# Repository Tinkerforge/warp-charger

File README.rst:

WARP Charger
============

You can find more information, technical details etc. about WARP Chargers at http://warp-charger.com.

This repository contains the source of this web site, all released firmwares, the manual and some additional information.

.. BEGIN WARP REPOSITORIES (managed block, generated from esp32-firmware/repo_overview.rst - do not edit by hand, run update_repo_overview.py instead)

WARP Repositories
-----------------

This is an overview of all repositories that make up the WARP Charger and
WARP Energy Manager ecosystem.

Please report **any** issue concerning WARP hard- or software in the
`esp32-firmware`_ repository, no matter which repository it originates from.

Software
~~~~~~~~

- `esp32-firmware`_ - Source code of the ESP32 firmware shared between all WARP Chargers and Energy Managers

Libraries used by the firmware:

- `tfjson`_ - SAX style JSON serializer and deserializer
- `tfnetwork`_ - Modbus TCP server and client implementation
- `tfocpp`_ - OCPP 1.6 implementation
- `tftools`_ - Miscellaneous tools and helpers

Remote access:

- `esp32-remote-access`_ - Source code of the my.warp-charger.com remote access server

Documentation, tools and integrations:

- `warp-charger`_ - Source code of (docs.)warp-charger.com and the printed manual, released firmwares, datasheets and documents, as well as some tools and hardware design files
- `api.warp-charger.com`_ - Serves APIs that are used by WARP Chargers to obtain relevant public information like day ahead prices
- `vislog.warp-charger.com`_ - Visualizes WARP Charger logs and EVSE debug protocols
- `dbus-warp-charger`_ - Integrates WARP Chargers into a Victron Energy Venus OS device (e.g. Cerbo GX)

WARP Charger Hardware
~~~~~~~~~~~~~~~~~~~~~~

WARP4 Charger
"""""""""""""

*Current charger generation.*

- `warp-esp32-ethernet-v2-brick`_ - Hardware design files of the WARP ESP32 Ethernet Brick 2.0
- `warp-esp32-ethernet-v2-co-bricklet`_ - Firmware source code of the WARP ESP32 Ethernet 2.0 Co Bricklet (co-processor)
- `evse-v4-bricklet`_ - Hardware design files of the EVSE 4.0 Bricklet (firmware shared with the EVSE 2.0 Bricklet)
- `nfc-bricklet`_ - Firmware source code and hardware design files of the NFC Bricklet

WARP3 Charger
"""""""""""""

- `warp-esp32-ethernet-brick`_ - Hardware design files of the WARP ESP32 Ethernet Brick
- `evse-v3-bricklet`_ - Hardware design files of the EVSE 3.0 Bricklet (firmware shared with the EVSE 2.0 Bricklet)
- `nfc-bricklet`_ - Firmware source code and hardware design files of the NFC Bricklet

WARP2 Charger
"""""""""""""

- `esp32-ethernet-brick`_ - Hardware design files of the ESP32 Ethernet Brick
- `evse-v2-bricklet`_ - Firmware source code and hardware design files of the EVSE 2.0 Bricklet
- `nfc-bricklet`_ - Firmware source code and hardware design files of the NFC Bricklet

WARP1 Charger
"""""""""""""

- `esp32-brick`_ - Hardware design files of the ESP32 Brick
- `evse-bricklet`_ - Firmware source code and hardware design files of the EVSE Bricklet
- `rs485-bricklet`_ - Firmware source code and hardware design files of the RS485 Bricklet

WARP Energy Manager Hardware
~~~~~~~~~~~~~~~~~~~~~~~~~~~~~~

WARP Energy Manager 2.0
"""""""""""""""""""""""

*Current energy manager generation.*

- `esp32-ethernet-brick`_ - Hardware design files of the ESP32 Ethernet Brick
- `warp-energy-manager-v2-bricklet`_ - Firmware source code and hardware design files of the WARP Energy Manager 2.0 Bricklet
- `warp-front-panel-bricklet`_ - Firmware source code and hardware design files of the WARP Front Panel Bricklet

WARP Energy Manager 1.0
"""""""""""""""""""""""

- `esp32-ethernet-brick`_ - Hardware design files of the ESP32 Ethernet Brick
- `warp-energy-manager-bricklet`_ - Firmware source code and hardware design files of the WARP Energy Manager Bricklet

Forked/patched projects
~~~~~~~~~~~~~~~~~~~~~~~~~

- `arduino-esp32`_
- `esp32-arduino-libs`_
- `WireGuard-ESP32-Arduino`_

.. Link targets: One definition per repository, keep in sync with the lists above.

.. _esp32-firmware: https://github.com/Tinkerforge/esp32-firmware
.. _tfjson: https://github.com/Tinkerforge/tfjson
.. _tfnetwork: https://github.com/Tinkerforge/tfnetwork
.. _tfocpp: https://github.com/Tinkerforge/tfocpp
.. _tftools: https://github.com/Tinkerforge/tftools
.. _esp32-remote-access: https://github.com/Tinkerforge/esp32-remote-access
.. _warp-charger: https://github.com/Tinkerforge/warp-charger
.. _api.warp-charger.com: https://github.com/Tinkerforge/api.warp-charger.com
.. _vislog.warp-charger.com: https://github.com/Tinkerforge/vislog.warp-charger.com
.. _dbus-warp-charger: https://github.com/Tinkerforge/dbus-warp-charger
.. _warp-esp32-ethernet-v2-brick: https://github.com/Tinkerforge/warp-esp32-ethernet-v2-brick
.. _warp-esp32-ethernet-v2-co-bricklet: https://github.com/Tinkerforge/warp-esp32-ethernet-v2-co-bricklet
.. _evse-v4-bricklet: https://github.com/Tinkerforge/evse-v4-bricklet
.. _nfc-bricklet: https://github.com/Tinkerforge/nfc-bricklet
.. _warp-esp32-ethernet-brick: https://github.com/Tinkerforge/warp-esp32-ethernet-brick
.. _evse-v3-bricklet: https://github.com/Tinkerforge/evse-v3-bricklet
.. _esp32-ethernet-brick: https://github.com/Tinkerforge/esp32-ethernet-brick
.. _evse-v2-bricklet: https://github.com/Tinkerforge/evse-v2-bricklet
.. _esp32-brick: https://github.com/Tinkerforge/esp32-brick
.. _evse-bricklet: https://github.com/Tinkerforge/evse-bricklet
.. _rs485-bricklet: https://github.com/Tinkerforge/rs485-bricklet
.. _warp-energy-manager-v2-bricklet: https://github.com/Tinkerforge/warp-energy-manager-v2-bricklet
.. _warp-front-panel-bricklet: https://github.com/Tinkerforge/warp-front-panel-bricklet
.. _warp-energy-manager-bricklet: https://github.com/Tinkerforge/warp-energy-manager-bricklet
.. _arduino-esp32: https://github.com/Tinkerforge/arduino-esp32
.. _esp32-arduino-libs: https://github.com/Tinkerforge/esp32-arduino-libs
.. _WireGuard-ESP32-Arduino: https://github.com/Tinkerforge/WireGuard-ESP32-Arduino

.. END WARP REPOSITORIES

Repository Content
------------------

documents/:
 * Contains test reports, data sheets and manuals for the WARP Charger itself and used components

firmwares/:
 * All released firmwares as well as their .elf files used for decoding stack traces and further debugging

hardware/:
 * Contains KiCad project files for some custom PCBs used in the WARP Charger

label/:
 * Scripts and other files used to create and print the type label sticker

manual/:
 * LaTeX source and used resources for the manual

warp-charger.com/:
 * The source of the WARP Charger web site (this site is deprecated, the old hand-written html site has been moved to a wordpress)

Firmwares
---------

The firmwares folder contains all released firmwares as bin files. These can be flashed
using the web interface or over USB using https://github.com/espressif/esptool/ at offset 0x1000.
The folder also contains the ELF files with debug information.

Hardware
--------

Parts of the hardware are designed with the open source EDA Suite KiCad
(http://www.kicad.org). Before you are able to open the files,
you have to install the Tinkerforge kicad-libraries
(https://github.com/Tinkerforge/kicad-libraries). You can either clone
them directly in hardware/ or clone them in a separate folder and
symlink them into hardware/
(ln -s kicad_path/kicad-libraries project_path/hardware). After that you
can open the .pro file in hardware/ with KiCad and from there view and
modify the schematics and the PCB layout.

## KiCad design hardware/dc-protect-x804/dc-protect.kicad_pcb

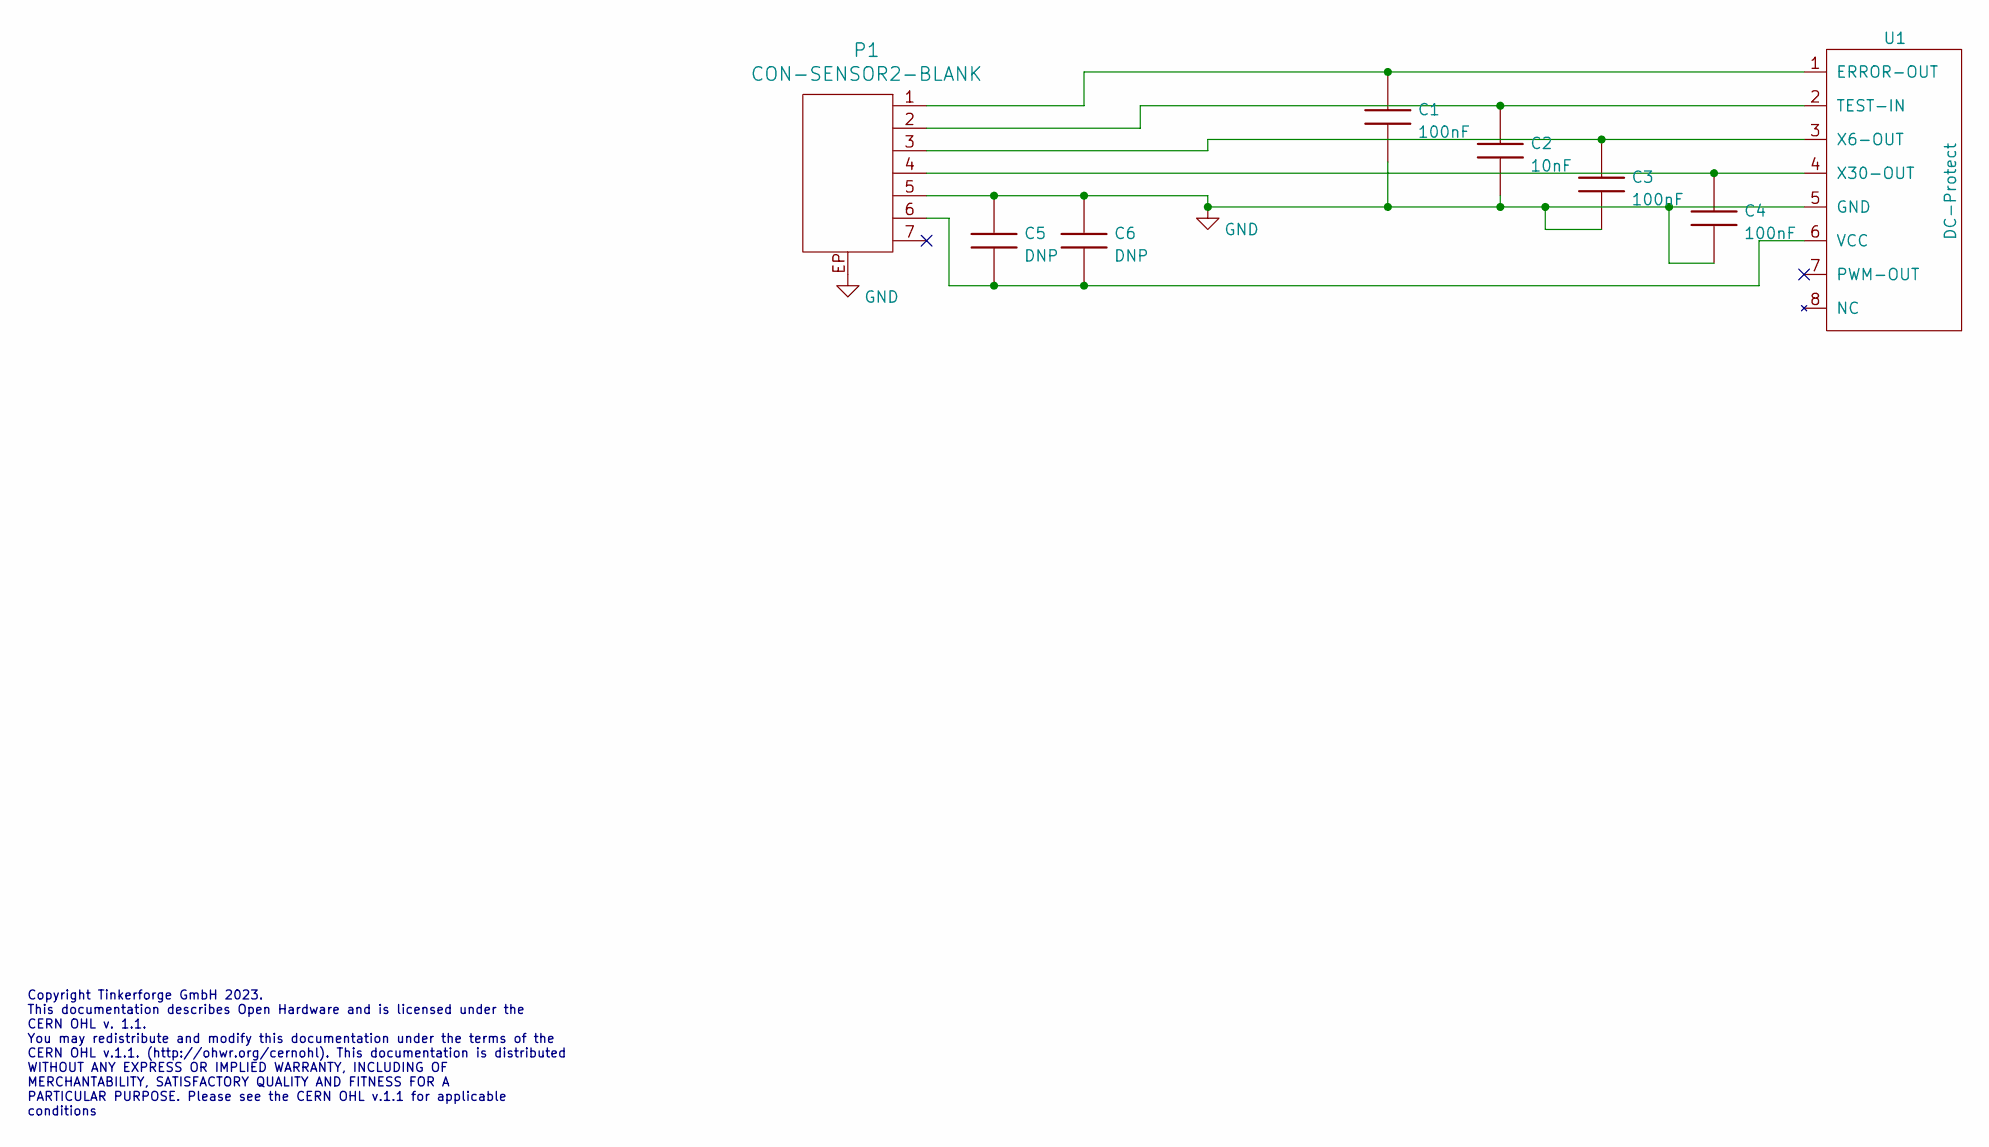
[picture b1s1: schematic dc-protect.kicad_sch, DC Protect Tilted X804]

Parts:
C1, C3, C4: 100nF; C0402E
C2: 10nF; C0402E
C5: DNP; C0805E
C6: DNP; C0402E
P1: CON-SENSOR2-BLANK; CON-SENSOR2_180
U1: DC-Protect

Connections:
GND: C1.2, C2.2, C3.2, C4.2, C5.1, C6.1, P1.5, P1.EP, U1.5 (GND)
unnamed: C1.1, P1.1, U1.1 (ERROR-OUT)
unnamed: C2.1, P1.2, U1.2 (TEST-IN)
unnamed: C3.1, P1.3, U1.3 (X6-OUT)
unnamed: C4.1, P1.4, U1.4 (X30-OUT)
unnamed: C5.2, C6.2, P1.6, U1.6 (VCC)

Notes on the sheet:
Copyright Tinkerforge GmbH 2023. This documentation describes Open Hardware and is licensed under the CERN OHL v. 1.1. You may redistribute and modify this documentation under the terms of the CERN OHL v.1.1. (http://ohwr.org/cernohl). This documentation is distributed WITHOUT ANY EXPRESS OR IMPLIE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

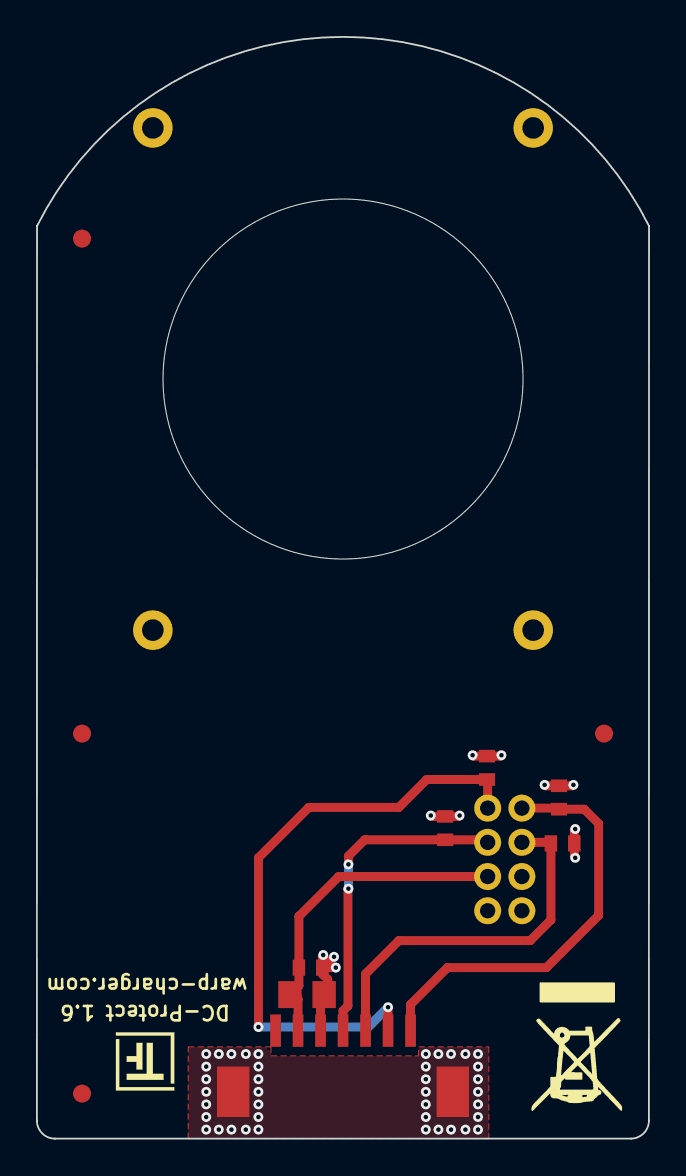
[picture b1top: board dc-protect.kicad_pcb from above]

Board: 2 copper layers, 34.0 x 61.2 mm, 13 parts (0 on the bottom side), 6 nets.

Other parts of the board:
Fiducial_Mark: VAL**; Fiducial_Mark
Fiducial_Mark#2, Fiducial_Mark#3, Fiducial_Mark#4: VAL**; Fiducial_Mark
VAL: WEEE_7mm

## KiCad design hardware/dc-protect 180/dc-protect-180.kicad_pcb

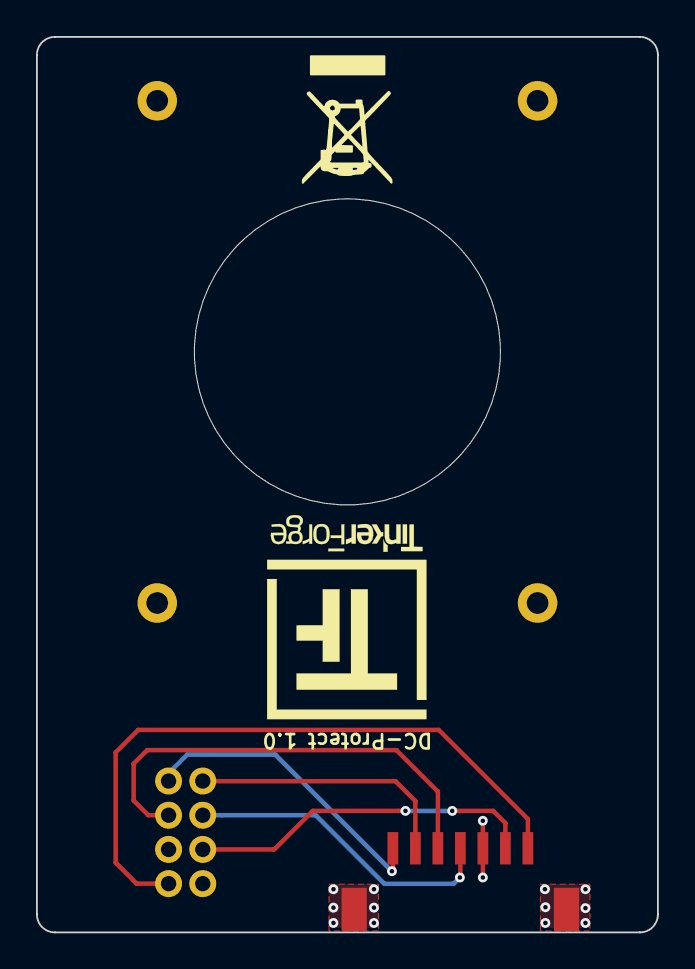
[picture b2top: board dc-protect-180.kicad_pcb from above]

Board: 2 copper layers, 34.5 x 49.8 mm, 3 parts (1 on the bottom side), 7 nets.

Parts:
P1: CON-SENSOR2-BLANK; CON-SENSOR2
U1: DC-Protect
VAL: WEEE_7mm

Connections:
GND: P1.5, P1.EP, U1.5
unnamed: P1.1, U1.1
unnamed: P1.2, U1.2
unnamed: P1.3, U1.3
unnamed: P1.4, U1.4
unnamed: P1.6, U1.6
unnamed: P1.7, U1.7

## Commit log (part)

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2026-05-28 docs: Move (WEM) charge tracker from energy manager to management.
2026-05-31 Move warp-charger.com to old.warp-charger.com
2026-05-31 Add new warp-charger.com homepage
2026-05-31 Remove unused server scripts (now handled by central cron.sh)
2026-05-31 WARP4-Charger -> WARP4 Charger
2026-05-31 build(deps): bump qs and express in /docs.warp-charger.com
    Bumps [qs](https://github.com/ljharb/qs) and [express](https://github.com/expressjs/express). These dependencies needed to be updated together.
    Updates `qs` from 6.14.2 to 6.15.2
    - [Changelog](https://github.com/ljharb/qs/blob/main/CHANGELOG.md)
    - [Commits](https://github.com/ljharb/qs/compare/v6.14.2...v6.15.2)
    Updates `express` from 4.22.1 to 4.22.2
    - [Release notes](https://github.com/expressjs/express/releases)
2026-05-31 Fix server npm directory
2026-05-31 add a lot of dots
2026-05-31 manuel: Improve wording, fix typos, remove todo-leftovers
2026-05-31 documents: Update WARP4 manual
2026-05-31 Improve naming consistency between english docs and web interface
2026-05-31 Fix charge management mixup
    confusingly it seems like we call the Charge Management "Charge Management",
    but then when we talk about the dynamic/static part about it, we
    call it load management.
2026-05-31 warp-charger.com: Fix Charge/Load Management mixup
2026-05-31 warp-charger.com: Add impact resistance
2026-05-31 warp-charger.com: Add anchors for documents
2026-05-31 warp-charger.com: Use same anchor name as old homepage
2026-06-01 Fix logo
2026-06-01 fix typo
2026-06-01 add faq
2026-06-01 appen technical specification
2026-06-01 warp-charger.com: Dont crop team photo on mobile
2026-06-01 Add company drone shot
2026-06-01 warp-charger.com: Add link for Made in Germany bento grid
2026-06-01 warp-charger.com: Fix icons and icon-links in mobile menu
2026-06-01 warp-charger.com: Improve language-switcher for mobile
2026-06-02 build(deps): bump webpack-dev-server in /docs.warp-charger.com
    Bumps [webpack-dev-server](https://github.com/webpack/webpack-dev-server) from 5.2.2 to 5.2.4.
    - [Release notes](https://github.com/webpack/webpack-dev-server/releases)
    - [Changelog](https://github.com/webpack/webpack-dev-server/blob/main/CHANGELOG.md)
    - [Commits](https://github.com/webpack/webpack-dev-server/compare/v5.2.2...v5.2.4)
    ---
    updated-dependencies:
2026-06-02 add features to technical details
2026-06-02 enhance technical spec
2026-06-02 improve technical spec
2026-06-02 increase charge tracker numbers: 7680 -> 32768 (new Firmware)
2026-06-02 docs: expand HA setup guide
2026-06-02 add more technical details
2026-06-02 build(deps): bump react from 19.2.6 to 19.2.7 in /docs.warp-charger.com
    Bumps [react](https://github.com/facebook/react/tree/HEAD/packages/react) from 19.2.6 to 19.2.7.
    - [Release notes](https://github.com/facebook/react/releases)
    - [Changelog](https://github.com/facebook/react/blob/main/CHANGELOG.md)
    - [Commits](https://github.com/facebook/react/commits/v19.2.7/packages/react)
    ---
    updated-dependencies:
2026-06-02 Add animation to image switcher
2026-06-02 warp-charger.com: Make the info button more visible
2026-06-02 Improve diagram step and pulse for mobile
2026-06-02 warp-charger.com: Make sure the info pulse stays of once pressed
2026-06-02 Use anchor for product tabs to make it sharable
2026-06-02 warp-charger.com: Implement newsletter registration
2026-06-03 build(deps): bump react-dom in /docs.warp-charger.com
    Bumps [react-dom](https://github.com/facebook/react/tree/HEAD/packages/react-dom) from 19.2.6 to 19.2.7.
    - [Release notes](https://github.com/facebook/react/releases)
    - [Changelog](https://github.com/facebook/react/blob/main/CHANGELOG.md)
    - [Commits](https://github.com/facebook/react/commits/v19.2.7/packages/react-dom)
    ---
    updated-dependencies:
2026-06-03 Add rounded borders and shadow to video
2026-06-03 warp-charger.com: Replace all ttfs with woff2.
2026-06-03 docs: Update modbus table.
2026-06-03 Add firmwares for WARP 2.11.0, WARP2 2.11.0, WARP3 2.11.0, WEM 2.7.0, WEM2 1.6.0, SEB 1.6.0.
2026-06-04 warp-charger.com: Update compile.sh for pre-compression
2026-06-04 warp-charger.com: Add find-an-electrician page
2026-06-04 warp-charger.com: Make electrician CTA more direct
2026-06-04 warp-charger.com: Just always call npm install when compile.sh is run
2026-06-04 Normalize phone numbers
2026-06-04 warp-charger.com: Add social share tags
    We need to make one 1200x630px image per page...
2026-06-05 add solaredge nexis support
2026-06-05 add kostal plenticore battery control
2026-06-05 fix eichrecht FAQ
2026-06-05 warp-charger.com: Update generated files.
2026-06-05 warp-charger.com: Let sections show up when 5% in viewport.
2026-06-05 docs: Document central management on chargers subpage.
2026-06-05 warp-charger.com: Normalize email addresses
    Use only email addresses that are part of the Impressum
2026-06-05 warp-charger.com: Remove double entry
2026-06-05 warp-charger.com: Update electricians
2026-06-05 add exhibition blogt
2026-06-05 fix faq
2026-06-05 warp-charger.com: Improve blog
2026-06-05 warp-charger.com: Improve electrician finder popup
2026-06-05 warp-charger.com: Allow swipe guesture for slider on mobile
2026-06-05 warp-charger.com: Add missing descriptive text for link
2026-06-05 warp-charger.com: Add mtime based cache-busting to static files
    We set "expires 1y;" in nginx
2026-06-05 warp-charger.com: Inline css to save a separate request
2026-06-05 warp-charger.com: Improve slider performance
2026-06-05 warp-charger.com: Make sure the video poster can be preloaded
2026-06-05 warp-charger.com: Defer diagram setup
2026-06-05 warp-charger.com: Add context to the "show more" link
    Even with aria info it was still flagged as bad seo/accessibility.
    It does look fine with the additional info the link directly.
2026-06-05 warp-charger.com: Improve font size and preload behavior
2026-06-05 warp-charger.com: Re-size/encode all images
    Now that the homepage is more mature we can resize all images
    to exact sizes that are actually needed.
2026-06-05 warp-charger.com: Re-encode images again
    Re-encode (from original) again. I was a bit too aggressive before.
    Some images got some obvious artifacts because of the qauality
    change in the webp encoding. We now just change the resolution
    of the images as needed, so there shouldn't be any recognizable
    difference in the image-quality now.
2026-06-08 warp-charger.com: Add bruns video
2026-06-08 warp-charger.com: Add WARP4 datasheet
2026-06-08 documents: Add WARP4_Datenblatt.pdf
2026-06-09 label: Patch length of SKU in data matrix code of package label
2026-06-09 docs: fix HA typos and grammar
2026-06-09 docs: add iobroker guide
2026-06-09 docs: add discovery options to MQTT introduction
2026-06-10 manual/warp4: Fix status widget colors.
2026-06-10 manual/warp4: Strip trailing whitespace.
2026-06-10 manual/warp4: Fix typos, wording, layout, etc.
2026-06-10 manual/warp4: Replace spare parts table with description.
2026-06-10 documents: Update WARP4 manual.
2026-06-10 add victron hint
2026-06-10 docs: fix typos and expand iobroker script
2026-06-10 label: Updates for WARP4
2026-06-10 label: Fix broken placeholder
2026-06-10 label: Fix WARP4 specific assert
2026-06-10 label: Fix version check
2026-06-10 label: Fix typo
2026-06-10 label: Use new wording for stand material
2026-06-10 label: Add custom cable to package label
2026-06-10 label: Add missing comma
2026-06-10 add preiskalender hint
2026-06-10 label: Fix title of internal label
2026-06-10 warp-charger.com: Update with bug-fixed videos
2026-06-10 docs: Update english translations
2026-06-10 docs: Improve english translations
    Fix some links, use consistant terminology etc
2026-06-11 build(deps): bump shell-quote in /docs.warp-charger.com
    Bumps [shell-quote](https://github.com/ljharb/shell-quote) from 1.8.3 to 1.8.4.
    - [Changelog](https://github.com/ljharb/shell-quote/blob/main/CHANGELOG.md)
    - [Commits](https://github.com/ljharb/shell-quote/compare/v1.8.3...v1.8.4)
    ---
    updated-dependencies:
    - dependency-name: shell-quote
2026-06-11 warp-charger.com: Update Made in Germany image
    Phoenix -> NMI
2026-06-11 docs: add openhab guide
2026-06-11 add elektrofreunde
2026-06-11 warp-charger.com: Fix grammer, typos
2026-06-12 docs: remove iobroker warning from MQTT introduction
2026-06-12 docs: add openhab translations and fix typos/grammar
2026-06-12 docs: update iobroker translation
2026-06-15 docs: Use consistant approach for different charger and EM generations
    Consistantly use "WARP Charger" and "WARP Energy Manager" to
    refer to any version. Only use WARPx Charger and WARP Energy Manager x.0
    when refering to a specific version.
2026-06-15 docs: Add proper backported docs for WARP1/2 and WEM1
2026-06-15 docs: Remove dependency and symlinks to tex-manual
    Also remove all unused images (only used in manual) and re-size
    some of the large images that need to be large for the print version
    of the manual.
    This idea to re-use the image folder from the manual got a bit out
    of hand because of the huge image sized that we have for WARP1/2
    manual.
2026-06-15 docs: Use same typography as warp-charger.com
    Just copies the font and most basic CSS.
2026-06-16 temporary fix of status page
2026-06-17 build(deps): bump dompurify in /docs.warp-charger.com
    Bumps [dompurify](https://github.com/cure53/DOMPurify) from 3.4.1 to 3.4.10.
    - [Release notes](https://github.com/cure53/DOMPurify/releases)
    - [Commits](https://github.com/cure53/DOMPurify/compare/3.4.1...3.4.10)
    ---
    updated-dependencies:
    - dependency-name: dompurify
2026-06-17 build(deps): bump launch-editor in /docs.warp-charger.com
    Bumps [launch-editor](https://github.com/vitejs/launch-editor) from 2.12.0 to 2.14.1.
    - [Commits](https://github.com/vitejs/launch-editor/compare/v2.12.0...v2.14.1)
    ---
    updated-dependencies:
    - dependency-name: launch-editor
    dependency-version: 2.14.1
2026-06-17 build(deps): bump ws in /docs.warp-charger.com
    Bumps and [ws](https://github.com/websockets/ws). These dependencies needed to be updated together.
    Updates `ws` from 7.5.10 to 7.5.11
    - [Release notes](https://github.com/websockets/ws/releases)
    - [Commits](https://github.com/websockets/ws/compare/7.5.10...7.5.11)
    Updates `ws` from 8.19.0 to 8.21.0
    - [Release notes](https://github.com/websockets/ws/releases)
2026-06-17 docs: add loxone setup guide (DE)
2026-06-17 docs: add template import image
2026-06-17 docs: Make sure xml files are downloaded
2026-06-18 firmwares: Add check for index file v3
2026-06-18 docs: add eebus notes to loxone
2026-06-19 add new blog
2026-06-19 add also blog
2026-06-20 docs: Add preliminary WARP4 installation video
2026-06-20 docs: Add WARP4 installation video
2026-06-22 warp-charger.com: Remove bogus entry
2026-06-22 warp-charger.com: Update gecoded json
2026-06-22 label: Rename the accessories label to extras label
    There will be an actual accessories label in the future.
    The now called extras label doesn't really include accessories,
    but modifications or additions to the normal charger build.
2026-06-23 label: Unify staging password file name.
2026-06-23 label: Also update .gitignore.
2026-06-24 docs: update eebus to include actors and client mode
2026-06-24 label: Add new accessories label
2026-06-25 firmwares: Add empty index file for WARP4
2026-06-25 Add firmwares for WARP 2.12.0, WARP2 2.12.0, WARP3 2.12.0, WARP4 2.12.0, WEM 2.8.0, WEM2 1.7.0, SEB 1.7.0.
2026-06-25 firmwares: Fix warp4 changelog.
2026-06-25 warp-charger.com: Add WARP4 firmware support
2026-06-25 firmwares: Add latest firmware link for provisioning script
2026-06-25 firmwares: Check symlink to latest OTA bin
2026-06-26 Add firmwares for WARP4 2.12.1.
2026-06-26 Make git treat *.bin files as binary
2026-06-26 Add electrician
2026-06-29 warp-charger.com: Remove power2drive banner
2026-06-30 label: Make custom type 2 argument optional for package label
2026-06-30 label: Fix package label data matrix layout for short SKU

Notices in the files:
hardware/dc-protect 180/dc-protect-180.kicad_pcb:
Licensed under CERN OHL v.1.1
Copyright (©) 2020, T.Schneidermann
Copyright Tinkerforge GmbH 2021.
hardware/dc-protect-x804/dc-protect.kicad_pcb:
Copyright (©) 2023, T.Schneidermann
